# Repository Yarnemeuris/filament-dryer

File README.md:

# filament-dryer
A simple filament dryer for drying 1 kg spools of filament. It's based around an Ender 3 heater and fan, combined with a PCB and another sensor. All controlled via Klipper. More information on CAD, firmware and the PCB is available in the folders.

## CAD
The filament is made for 3D printing and it will use about 350g of ABS/ASA. I deigned it in onshape, here is the [link](https://cad.onshape.com/documents/1bd024d5b7959acafc85207a/w/bc3f431890b8dcf2703dc2b2/e/cdbebe0165cb72dab1a66bad?configuration=open%3Dfalse&renderMode=0&uiState=6928c6e1034c4c312e27572e) if you want to see it yourself. Here are some more pictures from onshape:

## PCB
It uses a custom 2 layer pcb, that's designed to be hand soldered. Most of the components are through hole and the one that isn't is pretty zasy to do yourself. Here are some pictures of the pcb:

## BOM
In the BOM it uses a pico W because that is the only one LCSC has. You could also use a normal pico, but then you will need to get it from somewhere else.

| Category | Item | Quantity | Minimum Order Quantity | Unit Price | Total Price | URL | Running Total |
| ---: | ---: | ---: | ---: | ---: | ---: | ---: | ---: |
| PCB Components | Capacitor 10µF | 1 | 1 |  $ 0.3996  | $0.40 | https://www.lcsc.com/product-detail/C531341.html |  $ 0.40  |
| PCB Components | Capacitor 22µF | 1 | 1 |  $ 1.2269  | $1.23 | https://www.lcsc.com/product-detail/C531341.html |  $ 1.63  |
| PCB Components | JST XH connector | 5 | 10 |  $ 0.0482  | $0.48 | https://www.lcsc.com/product-detail/C378939.html |  $ 2.11  |
| PCB Components | Screw Terminal | 2 | 5 |  $ 0.1102  | $0.55 | https://www.lcsc.com/product-detail/C8465.html |  $ 2.66  |
| PCB Components | Mosfet | 2 | 1 |  $ 0.8775  | $1.76 | https://www.lcsc.com/product-detail/C38774.html |  $ 4.41  |
| PCB Components | Resistor 100Ω | 2 | 50 |  $ 0.0110  | $0.55 | https://www.lcsc.com/product-detail/C120214.html |  $ 4.96  |
| PCB Components | Resistor 100KΩ | 2 | 20 |  $ 0.0242  | $0.48 | https://www.lcsc.com/product-detail/C119444.html |  $ 5.45  |
| PCB Components | Resistor 120Ω | 1 | 20 |  $ 0.0122  | $0.24 | https://www.lcsc.com/product-detail/C359996.html |  $ 5.69  |
| PCB Components | Resistor 7KΩ | 1 | 20 |  $ 0.0229  | $0.46 | https://www.lcsc.com/product-detail/C119429.html |  $ 6.15  |
| PCB Components | CAN Transceiver | 1 | 1 |  $ 2.6161  | $2.62 | https://www.lcsc.com/product-detail/C16468.html |  $ 8.77  |
| PCB Components | Voltage Regulator | 1 | 1 |  $ 3.5895  | $3.59 | https://www.lcsc.com/product-detail/C22371890.html |  $ 12.36  |
| PCB Components | Jumper | 1 | 5 |  $ 0.0880  | $0.44 | https://www.lcsc.com/product-detail/C265313.html |  $ 12.80  |
| PCB Components | AHT21 Sensor | 1 | 1 |  $ 1.5105  | $1.51 | https://www.lcsc.com/product-detail/C3012624.html |  $ 14.31  |
| PCB Components | Pico W | 1 | 1 |  $ 10.7204  | $10.72 | https://www.lcsc.com/product-detail/C7203003.html |  $ 25.03  |
| PCB Components | 1x20 Pin Header | 2 | 5 |  $ 0.0566  | $0.28 | https://www.lcsc.com/product-detail/C42431804.html |  $ 25.31  |
| PCB Components | LCSC Shipping  | 1 |  |  $ 10.88  | $10.88 |  |  $ 36.19  |
| PCB | PCB (incl. shipping)  | 1 | 1 |  $ 4.24  | $4.24 | https://jlcpcb.com/ |  $ 40.43  |
| Parts | Heater | 1 |  | (from Ender 3) |  |  |  $ 40.43  |
| Parts | 4010 Blower Fan | 1 |  | (from Ender 3) |  |  |  $ 40.43  |
| Case | Printed Parts | 350g |  |  (I already own)  |  |  |  $ 40.43  |
| Case | Screws M3x12 | 4 |  |  (I already own)  |  |  |  $ 40.43  |
| Case | Screws M3x8 | 2 |  |  (I already own)  |  |  |  $ 40.43  |
| Case | Screws M3x16 | 2 |  |  (I already own)  |  |  |  $ 40.43  |
| Case | M3 Nuts | 6 |  |  (I already own)  |  |  |  $ 40.43  |
| Case | voron inserts | 2 |  |  (I already own)  |  |  |  $ 40.43  |

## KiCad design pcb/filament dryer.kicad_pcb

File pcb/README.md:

# PCB
The filament dryer uses a custom 2 layer pcb. I made it with almost only through hole components, so you don't need to order PCBA. But make sure when you order on both JLCPCB and LCSC that you chose global standard direct line. It is the cheapest option and bad things will happend if you don't. All the files needed for the pcb production and parts are in de production folder. The zip is the gerber files for JLCPCB and you can upload the bom.csv to LCSC. But add the extra sensor, pico and headers to your cart as well.

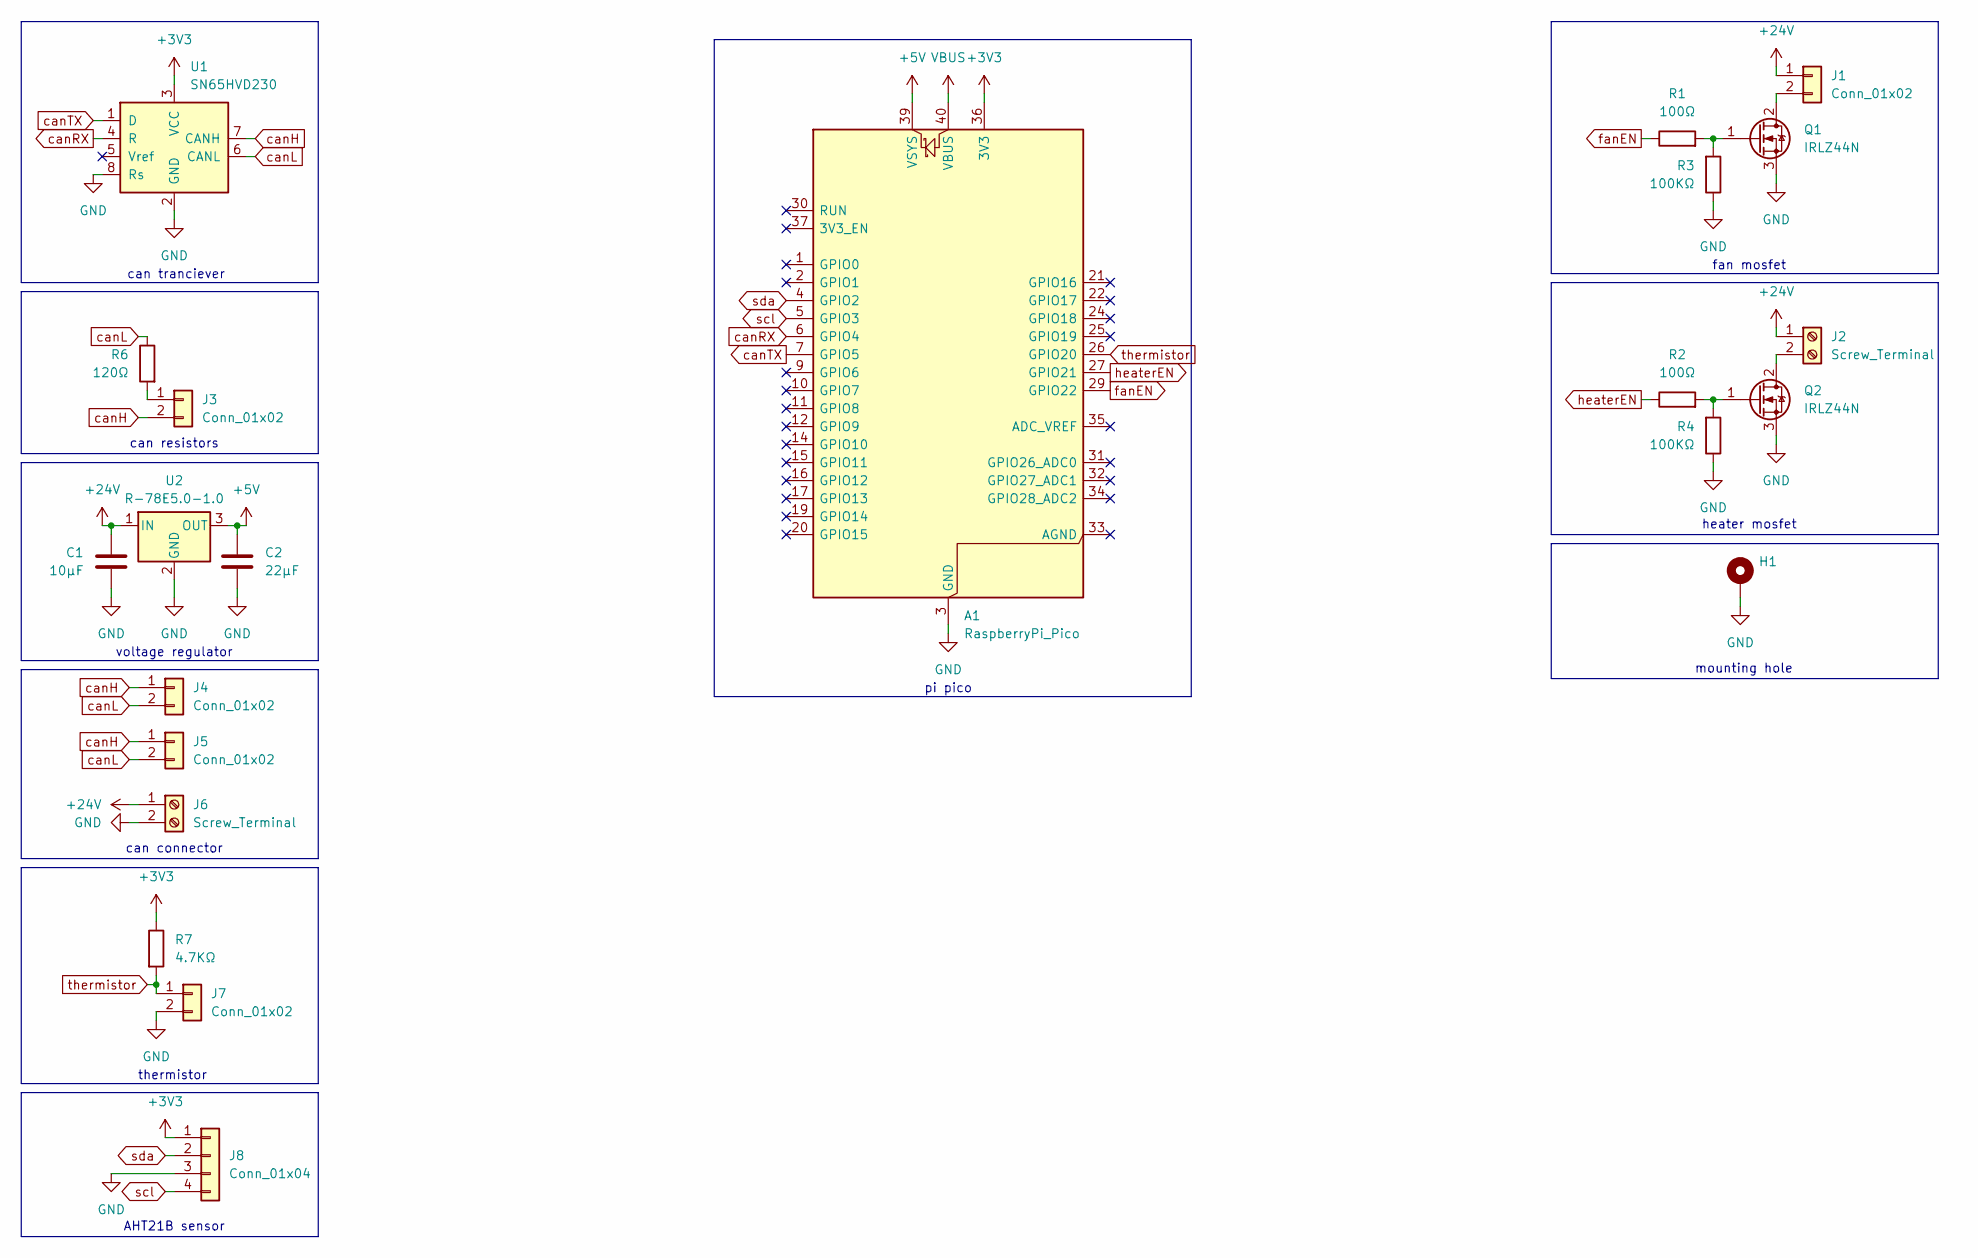
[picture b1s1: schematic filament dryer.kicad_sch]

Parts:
A1: RaspberryPi_Pico; RaspberryPi_Pico_Common_THT
C1: 10µF; C_Disc_D6.0mm_W4.4mm_P5.00mm; LCSC Part C531341
C2: 22µF; C_Disc_D6.0mm_W4.4mm_P5.00mm; LCSC Part C5259863
H1: MountingHole; MountingHole_3.2mm_M3_Pad
J1, J3, J4, J5, J7: Conn_01x02; JST_XH_B2B-XH-A_1x02_P2.50mm_Vertical; LCSC Part C378939
J2, J6: Screw_Terminal; TerminalBlock_CUI_TB007-508-02_1x02_P5.08mm_Horizontal; LCSC Part C8465
J8: Conn_01x04; PinSocket_1x04_P2.54mm_Vertical
Q1, Q2: IRLZ44N; TO-220-3_Horizontal_TabDown; LCSC Part C38774
R1, R2: 100Ω; R_Axial_DIN0309_L9.0mm_D3.2mm_P12.70mm_Horizontal; LCSC Part C120214
R3, R4: 100KΩ; R_Axial_DIN0309_L9.0mm_D3.2mm_P12.70mm_Horizontal; LCSC Part C119444
R6: 120Ω; R_Axial_DIN0309_L9.0mm_D3.2mm_P12.70mm_Horizontal; LCSC Part C359996
R7: 4.7KΩ; R_Axial_DIN0309_L9.0mm_D3.2mm_P12.70mm_Horizontal; LCSC Part C119429
U1: SN65HVD230; SOIC-8_3.9x4.9mm_P1.27mm; LCSC Part C16468
U2: R-78E5.0-1.0; Converter_DCDC_RECOM_R-78E-0.5_THT; LCSC Part C22371890

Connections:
+3V3: A1.36 (3V3), J8.1, R7.1, U1.3 (VCC)
+5V: A1.39 (VSYS), C2.1, U2.3 (OUT)
+24V: C1.1, J1.1, J2.1, J6.1, U2.1 (IN)
GND: A1.3 (GND), A1.8 (GND), A1.13 (GND), A1.18 (GND), A1.23 (GND), A1.28 (GND), A1.38 (GND), C1.2, C2.2, H1.1, J6.2, J7.2, J8.3, Q1.3 (S), Q2.3 (S), R3.1, R4.1, U1.2 (GND), U1.8 (Rs), U2.2 (GND)
unnamed: J1.2, Q1.2 (D)
unnamed: J2.2, Q2.2 (D)
unnamed: J3.1, R6.2
unnamed: Q1.1 (G), R1.2, R3.2
unnamed: Q2.1 (G), R2.2, R4.2
VBUS: A1.40 (VBUS)
canH: J3.2, J4.1, J5.1, U1.7 (CANH)
canL: J4.2, J5.2, R6.1, U1.6 (CANL)
canRX: A1.6 (GPIO4), U1.4 (R)
canTX: A1.7 (GPIO5), U1.1 (D)
fanEN: A1.29 (GPIO22), R1.1
heaterEN: A1.27 (GPIO21), R2.1
scl: A1.5 (GPIO3), J8.4
sda: A1.4 (GPIO2), J8.2
thermistor: A1.26 (GPIO20), J7.1, R7.2

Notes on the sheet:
fan mosfet
voltage regulator
can connector
heater mosfet
can tranciever
mounting hole
pi pico
can resistors
AHT21B sensor
thermistor

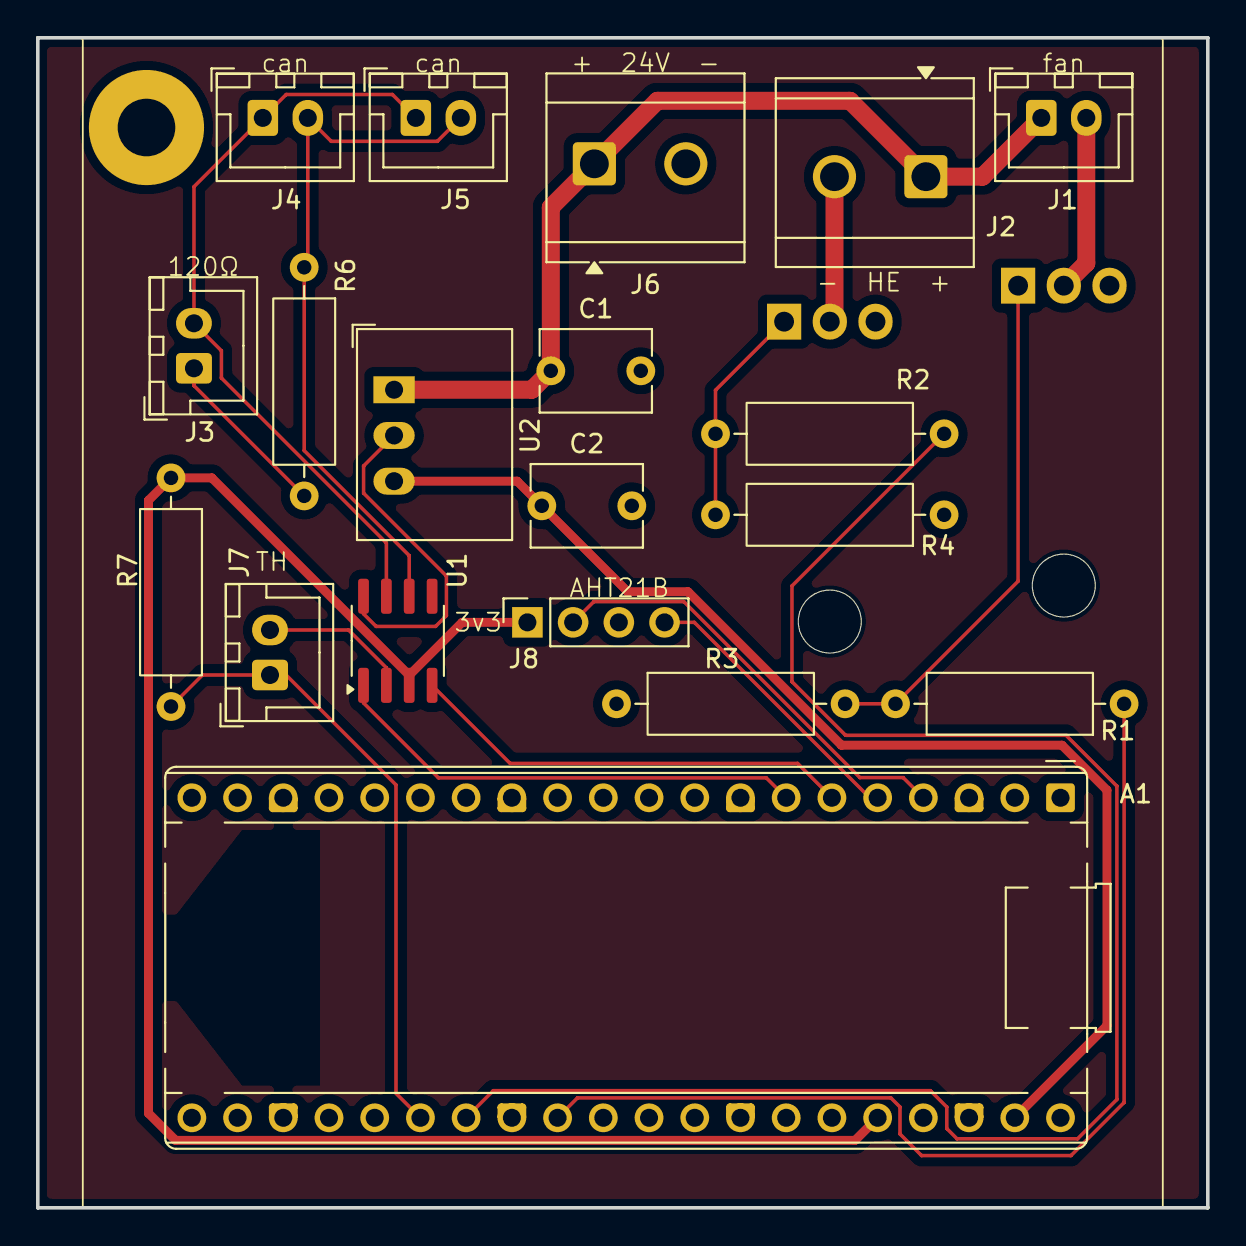
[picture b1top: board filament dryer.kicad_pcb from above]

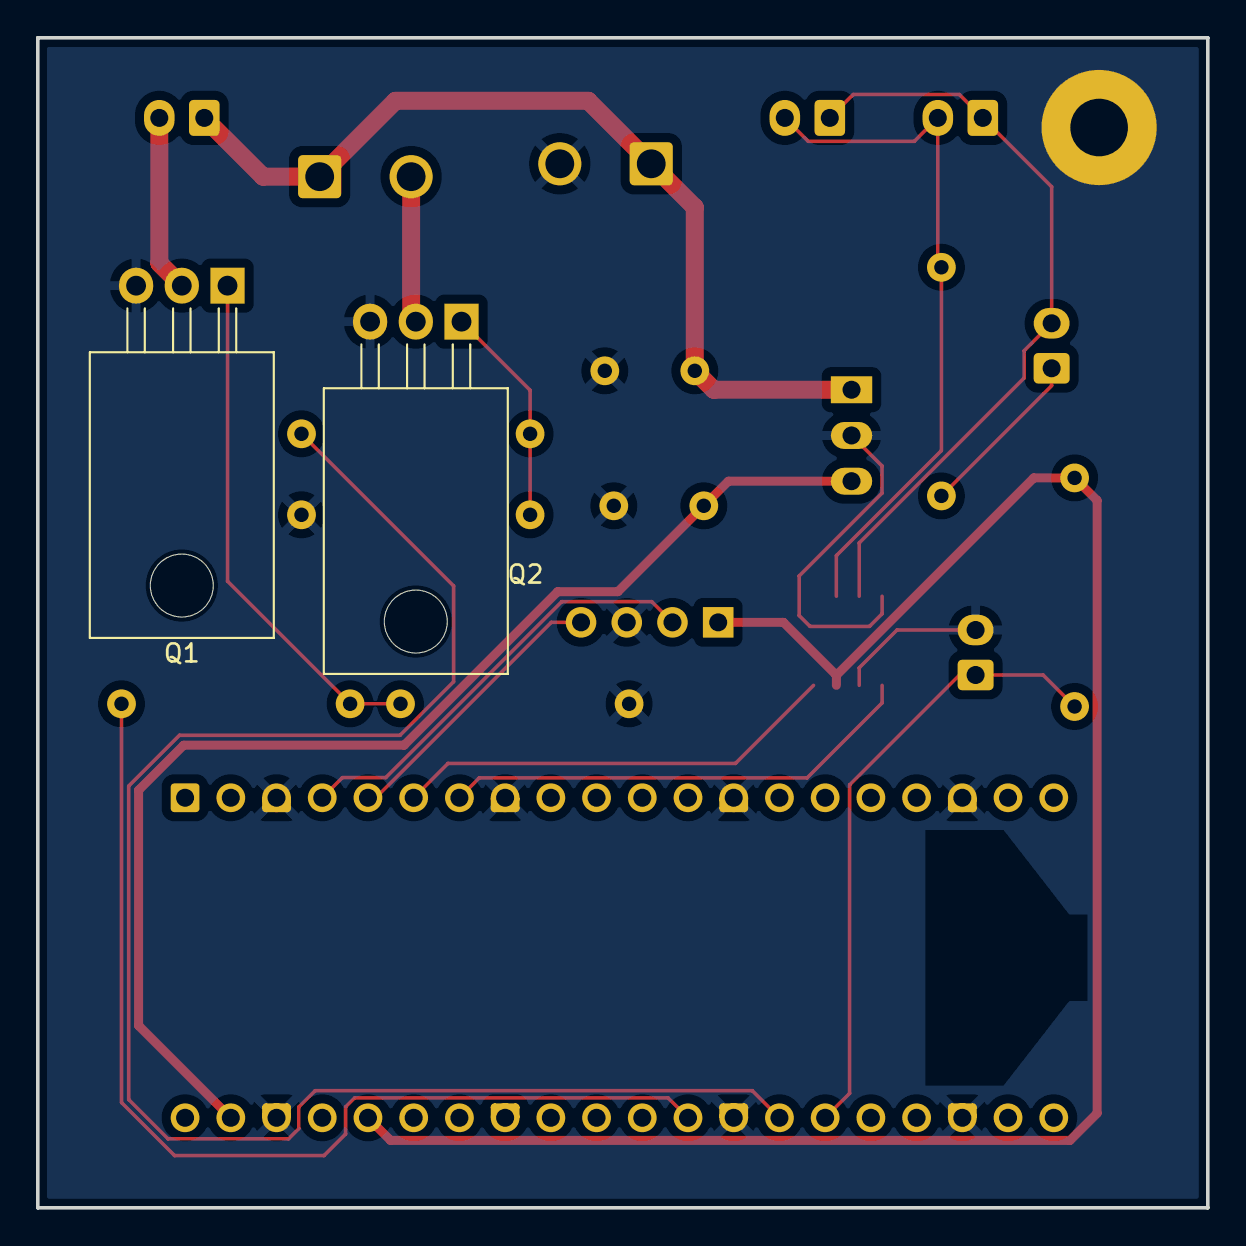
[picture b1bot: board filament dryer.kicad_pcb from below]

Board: 2 copper layers, 65.0 x 65.0 mm, 22 parts (2 on the bottom side), 18 nets.

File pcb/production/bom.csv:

Designator,Footprint,Quantity,Value,LCSC Part #
A1,RaspberryPi_Pico_Common_THT,1,RaspberryPi_Pico,
C1,C_Disc_D6.0mm_W4.4mm_P5.00mm,1,10µF,C531341
C2,C_Disc_D6.0mm_W4.4mm_P5.00mm,1,22µF,C5259863
"J1, J3, J4, J5, J7",JST_XH_B2B-XH-A_1x02_P2.50mm_Vertical,5,Conn_01x02,C378939
"J2, J6",TerminalBlock_CUI_TB007-508-02_1x02_P5.08mm_Horizontal,2,Screw_Terminal,C8465
"Q1, Q2",TO-220-3_Horizontal_TabDown,2,IRLZ44N,C38774
"R1, R2",R_Axial_DIN0309_L9.0mm_D3.2mm_P12.70mm_Horizontal,2,100Ω,C120214
"R3, R4",R_Axial_DIN0309_L9.0mm_D3.2mm_P12.70mm_Horizontal,2,100KΩ,C119444
R6,R_Axial_DIN0309_L9.0mm_D3.2mm_P12.70mm_Horizontal,1,120Ω,C359996
R7,R_Axial_DIN0309_L9.0mm_D3.2mm_P12.70mm_Horizontal,1,4.7KΩ,C119429
U1,SOIC-8_3.9x4.9mm_P1.27mm,1,SN65HVD230,C16468
U2,Converter_DCDC_RECOM_R-78E-0.5_THT,1,R-78E5.0-1.0,C22371890

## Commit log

2025-10-26 schematic
2025-11-27 PCB/CAD with README's
2025-11-29 pcb update and firmware
2025-11-30 Added the BOM
2025-11-30 README update
2025-12-03 added more detail and pictures to README
2025-12-04 added proof that I use global standard direct line
2025-12-04 Added README for PCB folder
